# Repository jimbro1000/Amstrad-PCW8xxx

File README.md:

# Amstrad PCW8xxx Schematics #
This repository contains a KiCad project representing
the schematics of the main board of the Amstrad
PCW8256 and PCW8512 personal computers

The project is complete for schematics only

The PCB design holds accurate board dimensions and
mostly accurate component positions. Where a component
is a critical reference location this has been 
measured and placed as accurately as possible.

# License #
This project is licensed under Creative Commons 4 BY-SA
See LICENSE file for full statement

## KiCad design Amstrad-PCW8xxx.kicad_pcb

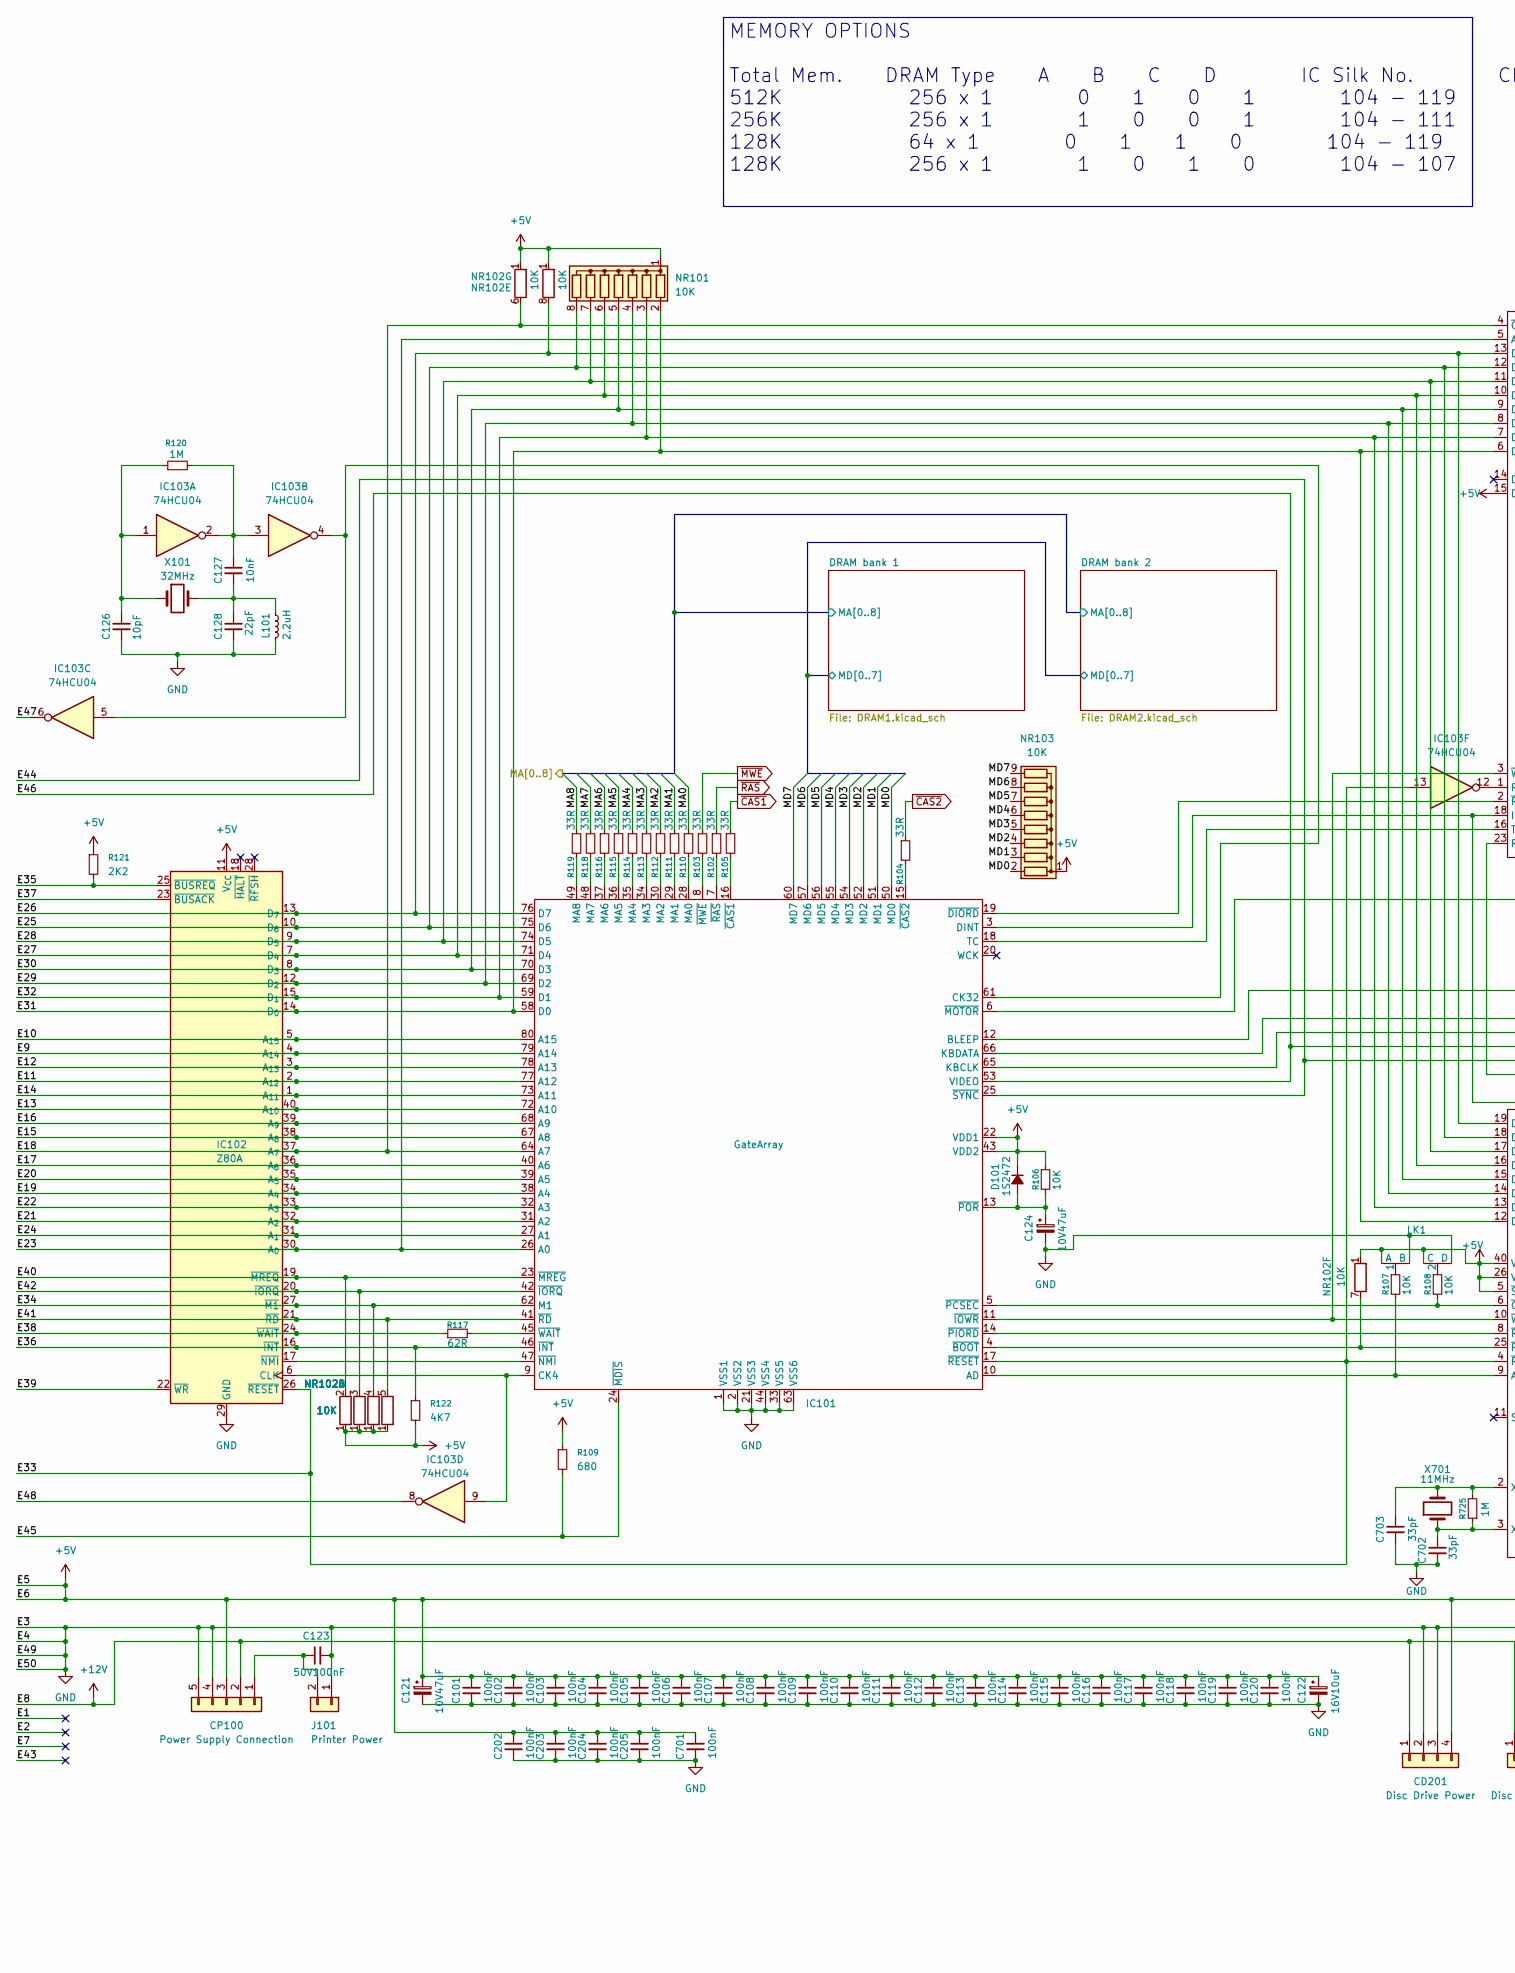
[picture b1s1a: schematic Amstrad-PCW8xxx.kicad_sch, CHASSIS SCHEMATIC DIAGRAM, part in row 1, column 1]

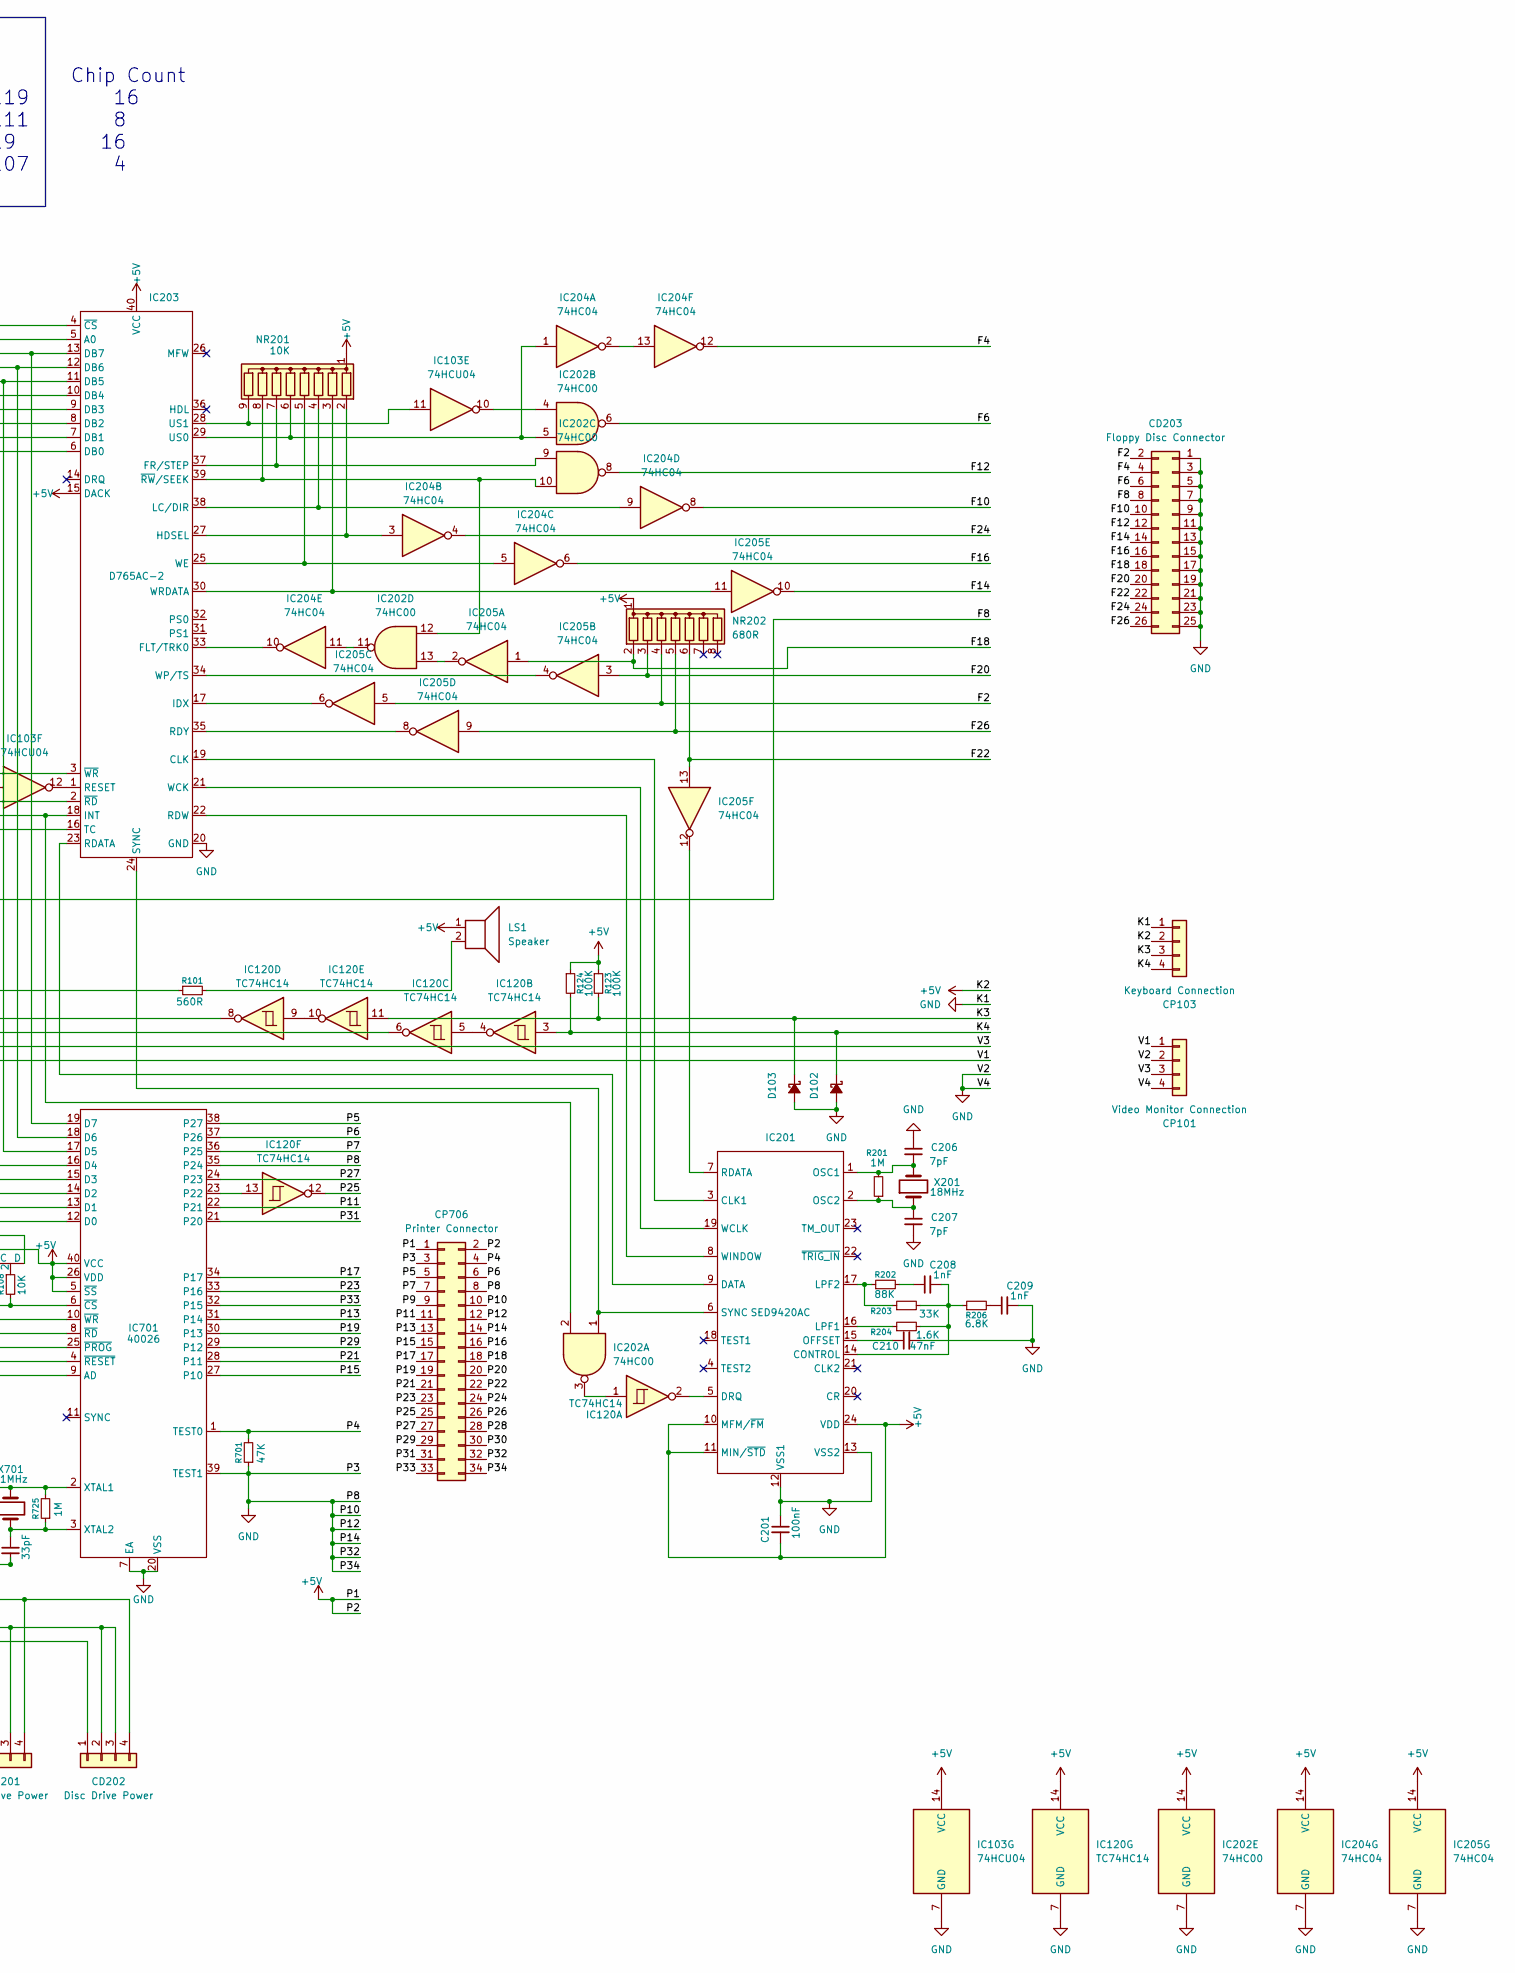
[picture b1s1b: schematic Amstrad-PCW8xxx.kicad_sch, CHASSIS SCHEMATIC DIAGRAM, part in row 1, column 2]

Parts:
C101, C102, C103, C104, C105, C106, C107, C108, C109, C110, C111, C112, C113, C114, C115, C116, C117, C118, C119, C120, C201, C202, C203, C204, C205, C701: 100nF; C_Disc_D9.0mm_W2.5mm_P5.00mm
C121, C124: 10V47uF; CP_Radial_P5.00mm
C122: 16V10uF; CP_Radial_P5.00mm
C123: 50V100nF; C_Disc_D9.0mm_W2.5mm_P5.00mm
C126: 10pF; C_Disc_D9.0mm_W2.5mm_P5.00mm
C127: 10nF; C_Disc_D9.0mm_W2.5mm_P5.00mm
C128: 22pF; C_Disc_D9.0mm_W2.5mm_P5.00mm
C206, C207: 7pF; C_Disc_D9.0mm_W2.5mm_P5.00mm
C208, C209: 1nF; C_Disc_D9.0mm_W2.5mm_P5.00mm
C210: 47nF; C_Disc_D9.0mm_W2.5mm_P5.00mm
C702, C703: 33pF; C_Disc_D9.0mm_W2.5mm_P5.00mm
CD201, CD202: Disc Drive Power; Molex_KK-254_AE-6410-04A_1x04_P2.54mm_Vertical
CD203: Floppy Disc Connector; IDC-Header_2x13_P2.54mm_Vertical
CP100: Power Supply Connection; Power Connection
CP101: Video Monitor Connection; Molex_KK-254_AE-6410-04A_1x04_P2.54mm_Vertical
CP103: Keyboard Connection; Molex_KK-254_AE-6410-04A_1x04_P2.54mm_Vertical
CP706: Printer Connector; IDC-Header_2x17_P2.54mm_Horizontal
D101: 1S2472; D_DO-35_SOD27_P10.16mm_Horizontal
D102, D103: D_DO-35_SOD27_P10.16mm_Horizontal
IC101: GateArray; Amstrad_PQFP-80_14x20mm_P0.8mm
IC102: Z80A; DIP-40_W15.24mm
IC103: 74HCU04; DIP-14_W7.62mm
IC120: TC74HC14; DIP-14_W7.62mm
IC201: SED9420AC; DIP-28_W15.24mm
IC202: 74HC00; DIP-14_W7.62mm
IC203: D765AC-2; DIP-40_W15.24mm
IC204, IC205: 74HC04; DIP-14_W7.62mm
IC701: 40026; DIP-40_W15.24mm
J101: Printer Power; BarrelJack_Horizontal
L101: 2.2uH; L_Axial_L6.6mm_D2.7mm_P10.16mm_Horizontal_Vishay_IM-2
LK1: Link_2
LS1: Speaker
NR101, NR102: 10K; R_Array_SIP8
NR103, NR201: 10K; R_Array_SIP9
NR202: 680R; R_Array_SIP8
R101: 560R; R_Axial_DIN0207_L6.3mm_D2.5mm_P10.16mm_Horizontal
R102, R103, R104, R105, R110, R111, R112, R113, R114, R115, R116, R118, R119: 33R; R_Axial_DIN0207_L6.3mm_D2.5mm_P10.16mm_Horizontal
R106, R107, R108: 10K; R_Axial_DIN0207_L6.3mm_D2.5mm_P10.16mm_Horizontal
R109: 680; R_Axial_DIN0207_L6.3mm_D2.5mm_P10.16mm_Horizontal
R117: 62R; R_Axial_DIN0207_L6.3mm_D2.5mm_P10.16mm_Horizontal
R120, R201, R725: 1M; R_Axial_DIN0207_L6.3mm_D2.5mm_P10.16mm_Horizontal
R121: 2K2; R_Axial_DIN0207_L6.3mm_D2.5mm_P10.16mm_Horizontal
R122: 4K7; R_Axial_DIN0207_L6.3mm_D2.5mm_P10.16mm_Horizontal
R123, R124: 100K; R_Axial_DIN0207_L6.3mm_D2.5mm_P10.16mm_Horizontal
R202: 88K; R_Axial_DIN0207_L6.3mm_D2.5mm_P10.16mm_Horizontal
R203: 33K; R_Axial_DIN0207_L6.3mm_D2.5mm_P10.16mm_Horizontal
R204: 1.6K; R_Axial_DIN0207_L6.3mm_D2.5mm_P10.16mm_Horizontal
R206: 6.8K; R_Axial_DIN0207_L6.3mm_D2.5mm_P10.16mm_Horizontal
R701: 47K; R_Axial_DIN0207_L6.3mm_D2.5mm_P10.16mm_Horizontal
X101: 32MHz; Crystal_HC49-U_Horizontal_1EP_style2
X201: 18MHz; Crystal_HC52-8mm_Vertical
X701: 11MHz; Crystal_HC52-8mm_Vertical

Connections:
+5V: C101.1, C102.1, C103.1, C104.1, C105.1, C106.1, C107.1, C108.1, C109.1, C110.1, C111.1, C112.1, C113.1, C114.1, C115.1, C116.1, C117.1, C118.1, C119.1, C120.1, C121.1, C122.1, C201.2, C202.1, C203.1, C204.1, C205.1, C701.1, CD201.4, CD202.4, CP100.3, CP103.2, CP706.1, CP706.2, D101.1 (K), IC101.22 (VDD1), IC101.43 (VDD2), IC102.11 (V_{CC}), IC103.14 (VCC), IC120.14 (VCC), IC201.10 (MFM/~FM), IC201.11 (MIN/~STD), IC201.24 (VDD), IC202.14 (VCC), IC203.15 (DACK), IC203.40 (VCC), IC204.14 (VCC), IC205.14 (VCC), IC701.5 (~SS), IC701.26 (VDD), IC701.40 (VCC), LK1.A, LK1.C, LS1.1, NR101.1 (common), NR102.1 (R1), NR103.1 (common), NR201.1 (common), NR202.1 (common), R106.1, R109.1, R121.1, R122.2, R123.1, R124.1; also elsewhere on the board
+12V: CD201.1, CD202.1, CP100.2
/DRAM bank 1/MD0: IC101.50 (MD0), NR103.2 (R1); also elsewhere on the board
/DRAM bank 1/MD1: IC101.51 (MD1), NR103.3 (R2); also elsewhere on the board
/DRAM bank 1/MD2: IC101.52 (MD2), NR103.4 (R3); also elsewhere on the board
/DRAM bank 1/MD3: IC101.54 (MD3), NR103.5 (R4); also elsewhere on the board
/DRAM bank 1/MD4: IC101.55 (MD4), NR103.6 (R5); also elsewhere on the board
/DRAM bank 1/MD5: IC101.56 (MD5), NR103.7 (R6); also elsewhere on the board
/DRAM bank 1/MD6: IC101.57 (MD6), NR103.8 (R7); also elsewhere on the board
/DRAM bank 1/MD7: IC101.60 (MD7), NR103.9 (R8); also elsewhere on the board
/E9: IC101.79 (A14), IC102.4 (A_{14})
/E10: IC101.80 (A15), IC102.5 (A_{15})
/E11: IC101.77 (A12), IC102.2 (A_{12})
/E12: IC101.78 (A13), IC102.3 (A_{13})
/E13: IC101.72 (A10), IC102.40 (A_{10})
/E14: IC101.73 (A11), IC102.1 (A_{11})
/E15: IC101.67 (A8), IC102.38 (A_{8})
/E16: IC101.68 (A9), IC102.39 (A_{9})
/E17: IC101.40 (A6), IC102.36 (A_{6})
/E18: IC101.64 (A7), IC102.37 (A_{7}), IC203.4 (~CS), NR102.6 (R5.2)
/E19: IC101.38 (A4), IC102.34 (A_{4})
/E20: IC101.39 (A5), IC102.35 (A_{5})
/E21: IC101.31 (A2), IC102.32 (A_{2})
/E22: IC101.32 (A3), IC102.33 (A_{3})
/E23: IC101.26 (A0), IC102.30 (A_{0}), IC203.5 (A0)
/E24: IC101.27 (A1), IC102.31 (A_{1})
/E25: IC101.75 (D6), IC102.10 (D_{6}), IC203.12 (DB6), IC701.18 (D6), NR101.8 (R7)
/E26: IC101.76 (D7), IC102.13 (D_{7}), IC203.13 (DB7), IC701.19 (D7), NR102.8 (R7.2)
/E27: IC101.71 (D4), IC102.7 (D_{4}), IC203.10 (DB4), IC701.16 (D4), NR101.6 (R5)
/E28: IC101.74 (D5), IC102.9 (D_{5}), IC203.11 (DB5), IC701.17 (D5), NR101.7 (R6)
/E29: IC101.69 (D2), IC102.12 (D_{2}), IC203.8 (DB2), IC701.14 (D2), NR101.4 (R3)
/E30: IC101.70 (D3), IC102.8 (D_{3}), IC203.9 (DB3), IC701.15 (D3), NR101.5 (R4)
/E31: IC101.58 (D0), IC102.14 (D_{0}), IC203.6 (DB0), IC701.12 (D0), NR101.2 (R1)
/E32: IC101.59 (D1), IC102.15 (D_{1}), IC203.7 (DB1), IC701.13 (D1), NR101.3 (R2)
/E33: IC101.17 (~RESET), IC102.26 (~RESET), IC103.13, IC701.4 (~RESET)
/E34: IC101.62 (M1), IC102.27 (~M1), NR102.4 (R3.2)
/E35: IC102.25 (~BUSREQ), R121.2
/E36: IC101.46 (~INT), IC102.16 (~INT), R122.1
/E37: IC102.23 (~BUSACK)
/E38: IC102.24 (~WAIT), R117.1
/E39: IC102.22 (~WR)
/E40: IC101.23 (~MREG), IC102.19 (~MREQ), NR102.2 (R1.2)
/E41: IC101.41 (~RD), IC102.21 (~RD), NR102.5 (R4.2)
/E42: IC101.42 (~IORQ), IC102.20 (~IORQ), NR102.3 (R2.2)
/E44: CP101.1, IC101.25 (~SYNC)
/E45: IC101.24 (~MDIS), R109.2
/E46: CP101.3, IC101.53 (VIDEO)
/E47: IC103.6
/E48: IC103.8
/F2: CD203.2, IC205.5, NR202.4 (R3)
/F4: CD203.4, IC204.12
/F6: CD203.6, IC202.6
/F8: CD203.8, IC101.6 (~MOTOR)
/F10: CD203.10, IC204.8
/F12: CD203.12, IC202.8
/F14: CD203.14, IC205.10
/F16: CD203.16, IC204.6
/F18: CD203.18, IC205.1, NR202.2 (R1)
/F20: CD203.20, IC205.3, NR202.3 (R2)
/F22: CD203.22, IC205.13, NR202.6 (R5)
/F24: CD203.24, IC204.4
/F26: CD203.26, IC205.9, NR202.5 (R4)
/K3: CP103.3, D103.1 (K), IC120.11, R123.2
/K4: CP103.4, D102.1 (K), IC120.3, R124.2
/MA0: R110.1; also elsewhere on the board
/MA1: R111.1; also elsewhere on the board
/MA2: R112.1; also elsewhere on the board
/MA3: R113.1; also elsewhere on the board
/MA4: R114.1; also elsewhere on the board
/MA5: R115.1; also elsewhere on the board
/MA6: R116.1; also elsewhere on the board
/MA7: R118.1; also elsewhere on the board
/MA8: R119.1; also elsewhere on the board
/P4: CP706.4, IC701.1 (TEST0), R701.2
/P5: CP706.5, IC701.38 (P27)
/P6: CP706.6, IC701.37 (P26)
/P7: CP706.7, IC701.36 (P25)
/P9: CP706.9
/P11: CP706.11, IC701.22 (P21)
/P13: CP706.13, IC701.31 (P14)
/P15: CP706.15, IC701.27 (P10)
/P16: CP706.16
/P17: CP706.17, IC701.34 (P17)
/P18: CP706.18
/P19: CP706.19, IC701.30 (P13)
/P20: CP706.20
/P21: CP706.21, IC701.28 (P11)
/P22: CP706.22
/P23: CP706.23, IC701.33 (P16)
/P24: CP706.24
/P25: CP706.25, IC120.12
/P26: CP706.26
/P27: CP706.27, IC701.24 (P23)
/P28: CP706.28
/P29: CP706.29, IC701.29 (P12)
/P30: CP706.30
/P31: CP706.31, IC701.21 (P20)
/P33: CP706.33, IC701.32 (P15)
GND: C101.2, C102.2, C103.2, C104.2, C105.2, C106.2, C107.2, C108.2, C109.2, C110.2, C111.2, C112.2, C113.2, C114.2, C115.2, C116.2, C117.2, C118.2, C119.2, C120.2, C121.2, C122.2, C123.2, C124.2, C126.2, C128.2, C201.1, C202.2, C203.2, C204.2, C205.2, C206.1, C207.2, C209.2, C210.2, C701.2, C702.2, C703.2, CD201.2, CD201.3, CD202.2, CD202.3, CD203.1, CD203.3, CD203.5, CD203.7, CD203.9, CD203.11, CD203.13, CD203.15, CD203.17, CD203.19, CD203.21, CD203.23, CD203.25, CP100.4, CP100.5, CP101.2, CP101.4, CP103.1, CP706.3, CP706.8, CP706.10, CP706.12, CP706.14, CP706.32, CP706.34, D102.2 (A), D103.2 (A), IC101.1 (VSS1), IC101.2 (VSS2), IC101.21 (VSS3), IC101.33 (VSS5), IC101.44 (VSS4), IC101.63 (VSS6), IC102.29 (GND), IC103.7 (GND), IC120.7 (GND), IC201.12 (VSS1), IC201.13 (VSS2), IC202.7 (GND), IC203.20 (GND), IC204.7 (GND), IC205.7 (GND), IC701.7 (EA), IC701.20 (VSS), IC701.35 (P24), IC701.39 (TEST1), J101.1, L101.2, LK1.B, LK1.D, R701.1; also elsewhere on the board
unnamed: C126.1, IC103.1, R120.1, X101.1
unnamed: C127.1, IC103.2, IC103.3, R120.2
unnamed: C127.2, C128.1, L101.1, X101.2
unnamed: C208.1, R202.2
unnamed: C209.1, R206.2
unnamed: C123.1, CP100.1, J101.2
unnamed: C124.1, D101.2 (A), IC101.13 (~POR), R106.2
unnamed: IC101.10 (AD), IC701.9 (AD), R107.2
unnamed: IC101.12 (BLEEP), R101.1
unnamed: IC101.9 (CK4), IC102.6 (CLK), IC103.9
unnamed: IC101.61 (CK32), IC103.4, IC103.5
unnamed: IC101.3 (DINT), IC202.2, IC203.18 (INT)
unnamed: IC101.65 (KBCLK), IC120.6
unnamed: IC101.66 (KBDATA), IC120.8
unnamed: IC101.28 (MA0), R110.2
unnamed: IC101.29 (MA1), R111.2
unnamed: IC101.30 (MA2), R112.2
unnamed: IC101.34 (MA3), R113.2
unnamed: IC101.35 (MA4), R114.2
unnamed: IC101.36 (MA5), R115.2
unnamed: IC101.37 (MA6), R116.2
unnamed: IC101.48 (MA7), R118.2
unnamed: IC101.49 (MA8), R119.2
unnamed: IC101.18 (TC), IC203.16 (TC)
unnamed: IC101.4 (~BOOT), IC701.25 (~PROG), NR102.7 (R6.2)
unnamed: IC101.16 (~CAS1), R105.2
unnamed: IC101.15 (~CAS2), R104.2
unnamed: IC101.19 (~DIORD), IC203.2 (~RD)
unnamed: IC101.11 (~IOWR), IC203.3 (~WR), IC701.10 (~WR)
unnamed: IC101.8 (~MWE), R103.2
unnamed: IC101.47 (~NMI), IC102.17 (~NMI)
unnamed: IC101.5 (~PCSEC), IC701.6 (~CS), R108.2
unnamed: IC101.14 (~PIORD), IC701.8 (~RD)
unnamed: IC101.7 (~RAS), R102.2
unnamed: IC101.45 (~WAIT), R117.2
unnamed: IC103.10, IC202.4
unnamed: IC120.1, IC202.3
unnamed: IC120.4, IC120.5
unnamed: IC120.9, IC120.10
unnamed: IC201.3 (CLK1), IC203.19 (CLK)
unnamed: C208.2, IC201.14 (CONTROL), R203.2, R204.2, R206.1
unnamed: IC201.9 (DATA), IC203.23 (RDATA)
unnamed: IC120.2, IC201.5 (DRQ)
unnamed: IC201.16 (LPF1), R204.1
unnamed: IC201.17 (LPF2), R202.1, R203.1
unnamed: C210.1, IC201.15 (OFFSET)
unnamed: C206.2, IC201.1 (OSC1), R201.2, X201.2
unnamed: C207.1, IC201.2 (OSC2), R201.1, X201.1
unnamed: IC201.7 (RDATA), IC205.12
unnamed: IC201.6 (SYNC), IC202.1, IC203.24 (SYNC)
unnamed: IC201.19 (WCLK), IC203.21 (WCK)
unnamed: IC201.8 (WINDOW), IC203.22 (RDW)
unnamed: IC202.11, IC204.11
unnamed: IC202.13, IC205.2
unnamed: IC203.33 (FLT/TRK0), IC204.10
unnamed: IC202.9, IC203.37 (FR/STEP), NR201.7 (R6)
unnamed: IC203.27 (HDSEL), IC204.3, NR201.2 (R1)
unnamed: IC203.17 (IDX), IC205.6
unnamed: IC203.38 (LC/DIR), IC204.9, NR201.4 (R3)
unnamed: IC203.35 (RDY), IC205.8
unnamed: IC103.12, IC203.1 (RESET)
unnamed: IC202.5, IC203.29 (US0), IC204.1, NR201.6 (R5)
unnamed: IC103.11, IC203.28 (US1), NR201.9 (R8)
unnamed: IC203.25 (WE), IC204.5, NR201.5 (R4)
unnamed: IC203.34 (WP/TS), IC205.4
unnamed: IC203.30 (WRDATA), IC205.11, NR201.3 (R2)
unnamed: IC202.10, IC202.12, IC203.39 (~RW/SEEK), NR201.8 (R7)
unnamed: IC204.2, IC204.13
unnamed: IC120.13, IC701.23 (P22)
unnamed: C703.1, IC701.2 (XTAL1), R725.2, X701.2
unnamed: C702.1, IC701.3 (XTAL2), R725.1, X701.1
unnamed: LK1.1, R107.1
unnamed: LK1.2, R108.1
unnamed: LS1.2, R101.2
~CAS1: R105.1; also elsewhere on the board
~CAS2: R104.1; also elsewhere on the board
~MWE: R103.1; also elsewhere on the board
~RAS: R102.1; also elsewhere on the board

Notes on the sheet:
MEMORY OPTIONS Total Mem. DRAM Type A B C D IC Silk No. Chip Count 512K 256 x 1 0 1 0 1 104 - 119 16 256K 256 x 1 1 0 0 1 104 - 111 8 128K 64 x 1 0 1 1 0 104 - 119 16 128K 256 x 1 1 0 1 0 104 - 107 4

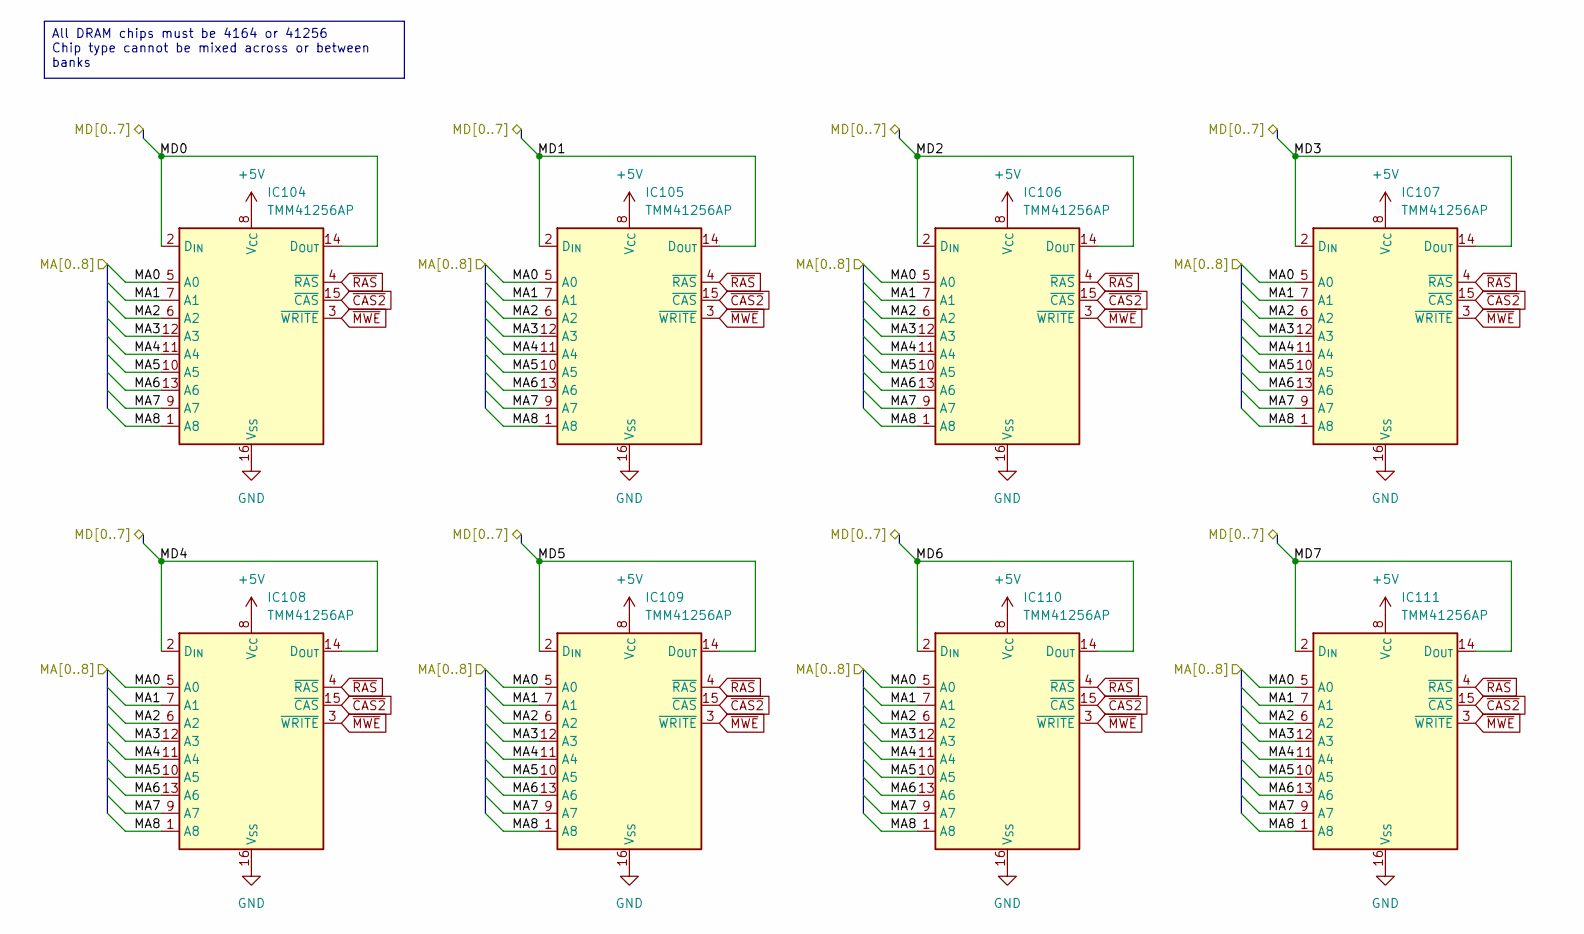
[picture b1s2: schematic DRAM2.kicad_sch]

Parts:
IC104, IC105, IC106, IC107, IC108, IC109, IC110, IC111: TMM41256AP; DIP-16_W7.62mm

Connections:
+5V: IC104.8 (V_{CC}), IC105.8 (V_{CC}), IC106.8 (V_{CC}), IC107.8 (V_{CC}), IC108.8 (V_{CC}), IC109.8 (V_{CC}), IC110.8 (V_{CC}), IC111.8 (V_{CC}); also elsewhere on the board
/DRAM bank 1/MD0: IC104.2 (D_{IN}), IC104.14 (D_{OUT}); also elsewhere on the board
/DRAM bank 1/MD1: IC105.2 (D_{IN}), IC105.14 (D_{OUT}); also elsewhere on the board
/DRAM bank 1/MD2: IC106.2 (D_{IN}), IC106.14 (D_{OUT}); also elsewhere on the board
/DRAM bank 1/MD3: IC107.2 (D_{IN}), IC107.14 (D_{OUT}); also elsewhere on the board
/DRAM bank 1/MD4: IC108.2 (D_{IN}), IC108.14 (D_{OUT}); also elsewhere on the board
/DRAM bank 1/MD5: IC109.2 (D_{IN}), IC109.14 (D_{OUT}); also elsewhere on the board
/DRAM bank 1/MD6: IC110.2 (D_{IN}), IC110.14 (D_{OUT}); also elsewhere on the board
/DRAM bank 1/MD7: IC111.2 (D_{IN}), IC111.14 (D_{OUT}); also elsewhere on the board
/MA0: IC104.5 (A0), IC105.5 (A0), IC106.5 (A0), IC107.5 (A0), IC108.5 (A0), IC109.5 (A0), IC110.5 (A0), IC111.5 (A0); also elsewhere on the board
/MA1: IC104.7 (A1), IC105.7 (A1), IC106.7 (A1), IC107.7 (A1), IC108.7 (A1), IC109.7 (A1), IC110.7 (A1), IC111.7 (A1); also elsewhere on the board
/MA2: IC104.6 (A2), IC105.6 (A2), IC106.6 (A2), IC107.6 (A2), IC108.6 (A2), IC109.6 (A2), IC110.6 (A2), IC111.6 (A2); also elsewhere on the board
/MA3: IC104.12 (A3), IC105.12 (A3), IC106.12 (A3), IC107.12 (A3), IC108.12 (A3), IC109.12 (A3), IC110.12 (A3), IC111.12 (A3); also elsewhere on the board
/MA4: IC104.11 (A4), IC105.11 (A4), IC106.11 (A4), IC107.11 (A4), IC108.11 (A4), IC109.11 (A4), IC110.11 (A4), IC111.11 (A4); also elsewhere on the board
/MA5: IC104.10 (A5), IC105.10 (A5), IC106.10 (A5), IC107.10 (A5), IC108.10 (A5), IC109.10 (A5), IC110.10 (A5), IC111.10 (A5); also elsewhere on the board
/MA6: IC104.13 (A6), IC105.13 (A6), IC106.13 (A6), IC107.13 (A6), IC108.13 (A6), IC109.13 (A6), IC110.13 (A6), IC111.13 (A6); also elsewhere on the board
/MA7: IC104.9 (A7), IC105.9 (A7), IC106.9 (A7), IC107.9 (A7), IC108.9 (A7), IC109.9 (A7), IC110.9 (A7), IC111.9 (A7); also elsewhere on the board
/MA8: IC104.1 (A8), IC105.1 (A8), IC106.1 (A8), IC107.1 (A8), IC108.1 (A8), IC109.1 (A8), IC110.1 (A8), IC111.1 (A8); also elsewhere on the board
GND: IC104.16 (V_{SS}), IC105.16 (V_{SS}), IC106.16 (V_{SS}), IC107.16 (V_{SS}), IC108.16 (V_{SS}), IC109.16 (V_{SS}), IC110.16 (V_{SS}), IC111.16 (V_{SS}); also elsewhere on the board
~CAS2: IC104.15 (~CAS), IC105.15 (~CAS), IC106.15 (~CAS), IC107.15 (~CAS), IC108.15 (~CAS), IC109.15 (~CAS), IC110.15 (~CAS), IC111.15 (~CAS); also elsewhere on the board
~MWE: IC104.3 (~WRITE), IC105.3 (~WRITE), IC106.3 (~WRITE), IC107.3 (~WRITE), IC108.3 (~WRITE), IC109.3 (~WRITE), IC110.3 (~WRITE), IC111.3 (~WRITE); also elsewhere on the board
~RAS: IC104.4 (~RAS), IC105.4 (~RAS), IC106.4 (~RAS), IC107.4 (~RAS), IC108.4 (~RAS), IC109.4 (~RAS), IC110.4 (~RAS), IC111.4 (~RAS); also elsewhere on the board

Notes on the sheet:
All DRAM chips must be 4164 or 41256 Chip type cannot be mixed across or between banks

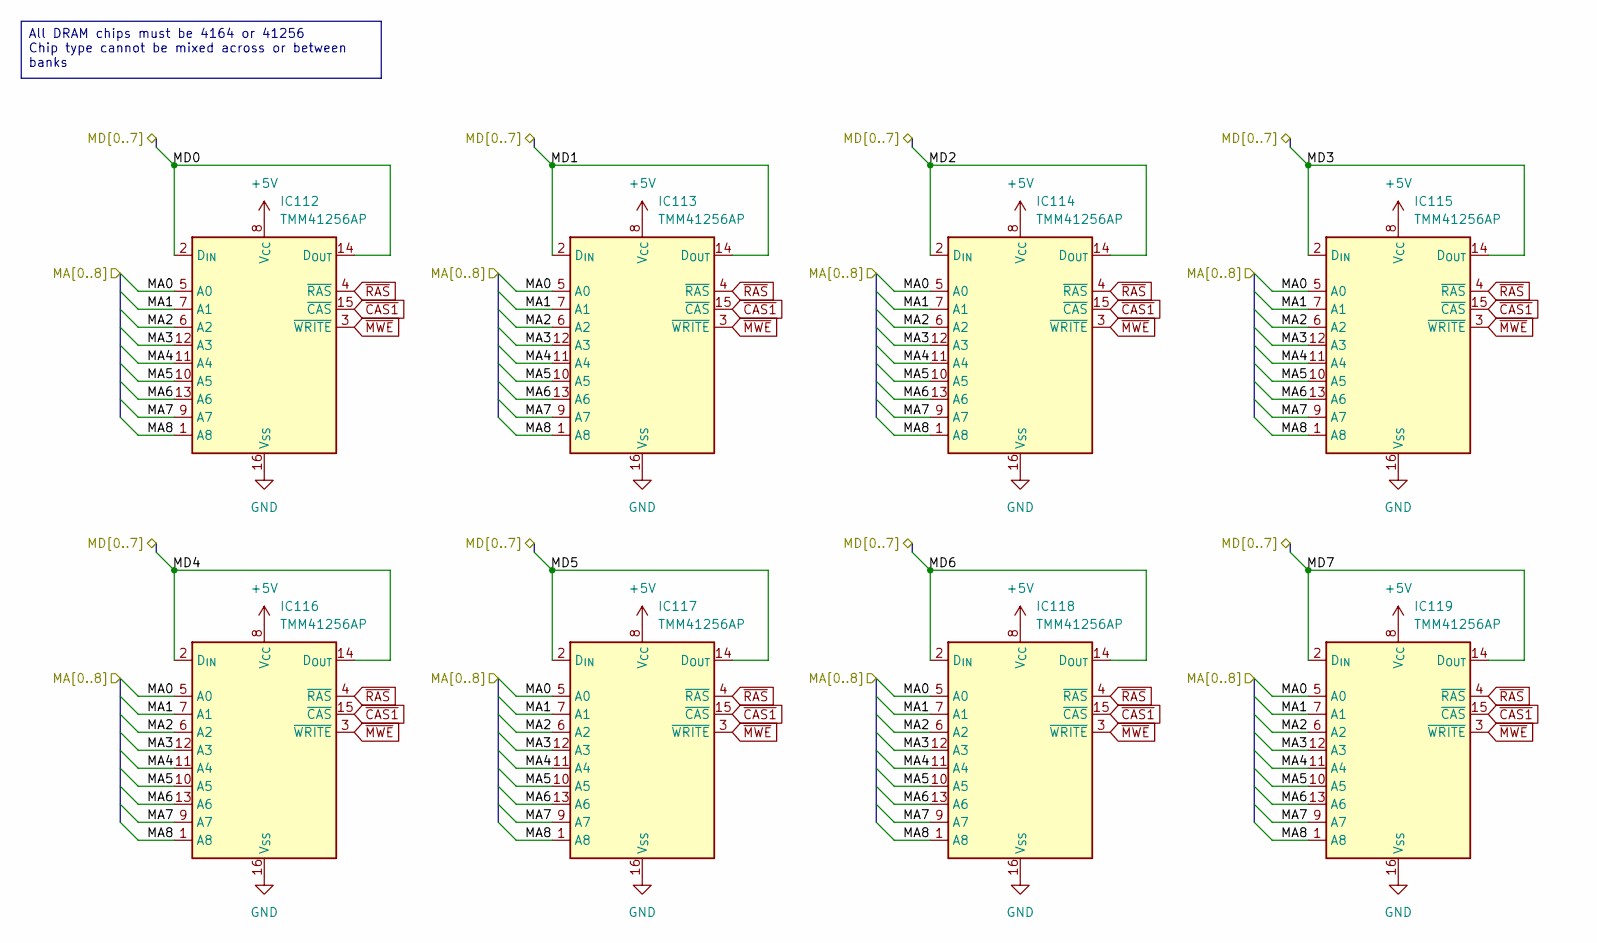
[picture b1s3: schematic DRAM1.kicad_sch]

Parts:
IC112, IC113, IC114, IC115, IC116, IC117, IC118, IC119: TMM41256AP; DIP-16_W7.62mm

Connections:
+5V: IC112.8 (V_{CC}), IC113.8 (V_{CC}), IC114.8 (V_{CC}), IC115.8 (V_{CC}), IC116.8 (V_{CC}), IC117.8 (V_{CC}), IC118.8 (V_{CC}), IC119.8 (V_{CC}); also elsewhere on the board
/DRAM bank 1/MD0: IC112.2 (D_{IN}), IC112.14 (D_{OUT}); also elsewhere on the board
/DRAM bank 1/MD1: IC113.2 (D_{IN}), IC113.14 (D_{OUT}); also elsewhere on the board
/DRAM bank 1/MD2: IC114.2 (D_{IN}), IC114.14 (D_{OUT}); also elsewhere on the board
/DRAM bank 1/MD3: IC115.2 (D_{IN}), IC115.14 (D_{OUT}); also elsewhere on the board
/DRAM bank 1/MD4: IC116.2 (D_{IN}), IC116.14 (D_{OUT}); also elsewhere on the board
/DRAM bank 1/MD5: IC117.2 (D_{IN}), IC117.14 (D_{OUT}); also elsewhere on the board
/DRAM bank 1/MD6: IC118.2 (D_{IN}), IC118.14 (D_{OUT}); also elsewhere on the board
/DRAM bank 1/MD7: IC119.2 (D_{IN}), IC119.14 (D_{OUT}); also elsewhere on the board
/MA0: IC112.5 (A0), IC113.5 (A0), IC114.5 (A0), IC115.5 (A0), IC116.5 (A0), IC117.5 (A0), IC118.5 (A0), IC119.5 (A0); also elsewhere on the board
/MA1: IC112.7 (A1), IC113.7 (A1), IC114.7 (A1), IC115.7 (A1), IC116.7 (A1), IC117.7 (A1), IC118.7 (A1), IC119.7 (A1); also elsewhere on the board
/MA2: IC112.6 (A2), IC113.6 (A2), IC114.6 (A2), IC115.6 (A2), IC116.6 (A2), IC117.6 (A2), IC118.6 (A2), IC119.6 (A2); also elsewhere on the board
/MA3: IC112.12 (A3), IC113.12 (A3), IC114.12 (A3), IC115.12 (A3), IC116.12 (A3), IC117.12 (A3), IC118.12 (A3), IC119.12 (A3); also elsewhere on the board
/MA4: IC112.11 (A4), IC113.11 (A4), IC114.11 (A4), IC115.11 (A4), IC116.11 (A4), IC117.11 (A4), IC118.11 (A4), IC119.11 (A4); also elsewhere on the board
/MA5: IC112.10 (A5), IC113.10 (A5), IC114.10 (A5), IC115.10 (A5), IC116.10 (A5), IC117.10 (A5), IC118.10 (A5), IC119.10 (A5); also elsewhere on the board
/MA6: IC112.13 (A6), IC113.13 (A6), IC114.13 (A6), IC115.13 (A6), IC116.13 (A6), IC117.13 (A6), IC118.13 (A6), IC119.13 (A6); also elsewhere on the board
/MA7: IC112.9 (A7), IC113.9 (A7), IC114.9 (A7), IC115.9 (A7), IC116.9 (A7), IC117.9 (A7), IC118.9 (A7), IC119.9 (A7); also elsewhere on the board
/MA8: IC112.1 (A8), IC113.1 (A8), IC114.1 (A8), IC115.1 (A8), IC116.1 (A8), IC117.1 (A8), IC118.1 (A8), IC119.1 (A8); also elsewhere on the board
GND: IC112.16 (V_{SS}), IC113.16 (V_{SS}), IC114.16 (V_{SS}), IC115.16 (V_{SS}), IC116.16 (V_{SS}), IC117.16 (V_{SS}), IC118.16 (V_{SS}), IC119.16 (V_{SS}); also elsewhere on the board
~CAS1: IC112.15 (~CAS), IC113.15 (~CAS), IC114.15 (~CAS), IC115.15 (~CAS), IC116.15 (~CAS), IC117.15 (~CAS), IC118.15 (~CAS), IC119.15 (~CAS); also elsewhere on the board
~MWE: IC112.3 (~WRITE), IC113.3 (~WRITE), IC114.3 (~WRITE), IC115.3 (~WRITE), IC116.3 (~WRITE), IC117.3 (~WRITE), IC118.3 (~WRITE), IC119.3 (~WRITE); also elsewhere on the board
~RAS: IC112.4 (~RAS), IC113.4 (~RAS), IC114.4 (~RAS), IC115.4 (~RAS), IC116.4 (~RAS), IC117.4 (~RAS), IC118.4 (~RAS), IC119.4 (~RAS); also elsewhere on the board

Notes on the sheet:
All DRAM chips must be 4164 or 41256 Chip type cannot be mixed across or between banks

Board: 2 copper layers, 119 parts (0 on the bottom side), 164 nets, no tracks yet.
